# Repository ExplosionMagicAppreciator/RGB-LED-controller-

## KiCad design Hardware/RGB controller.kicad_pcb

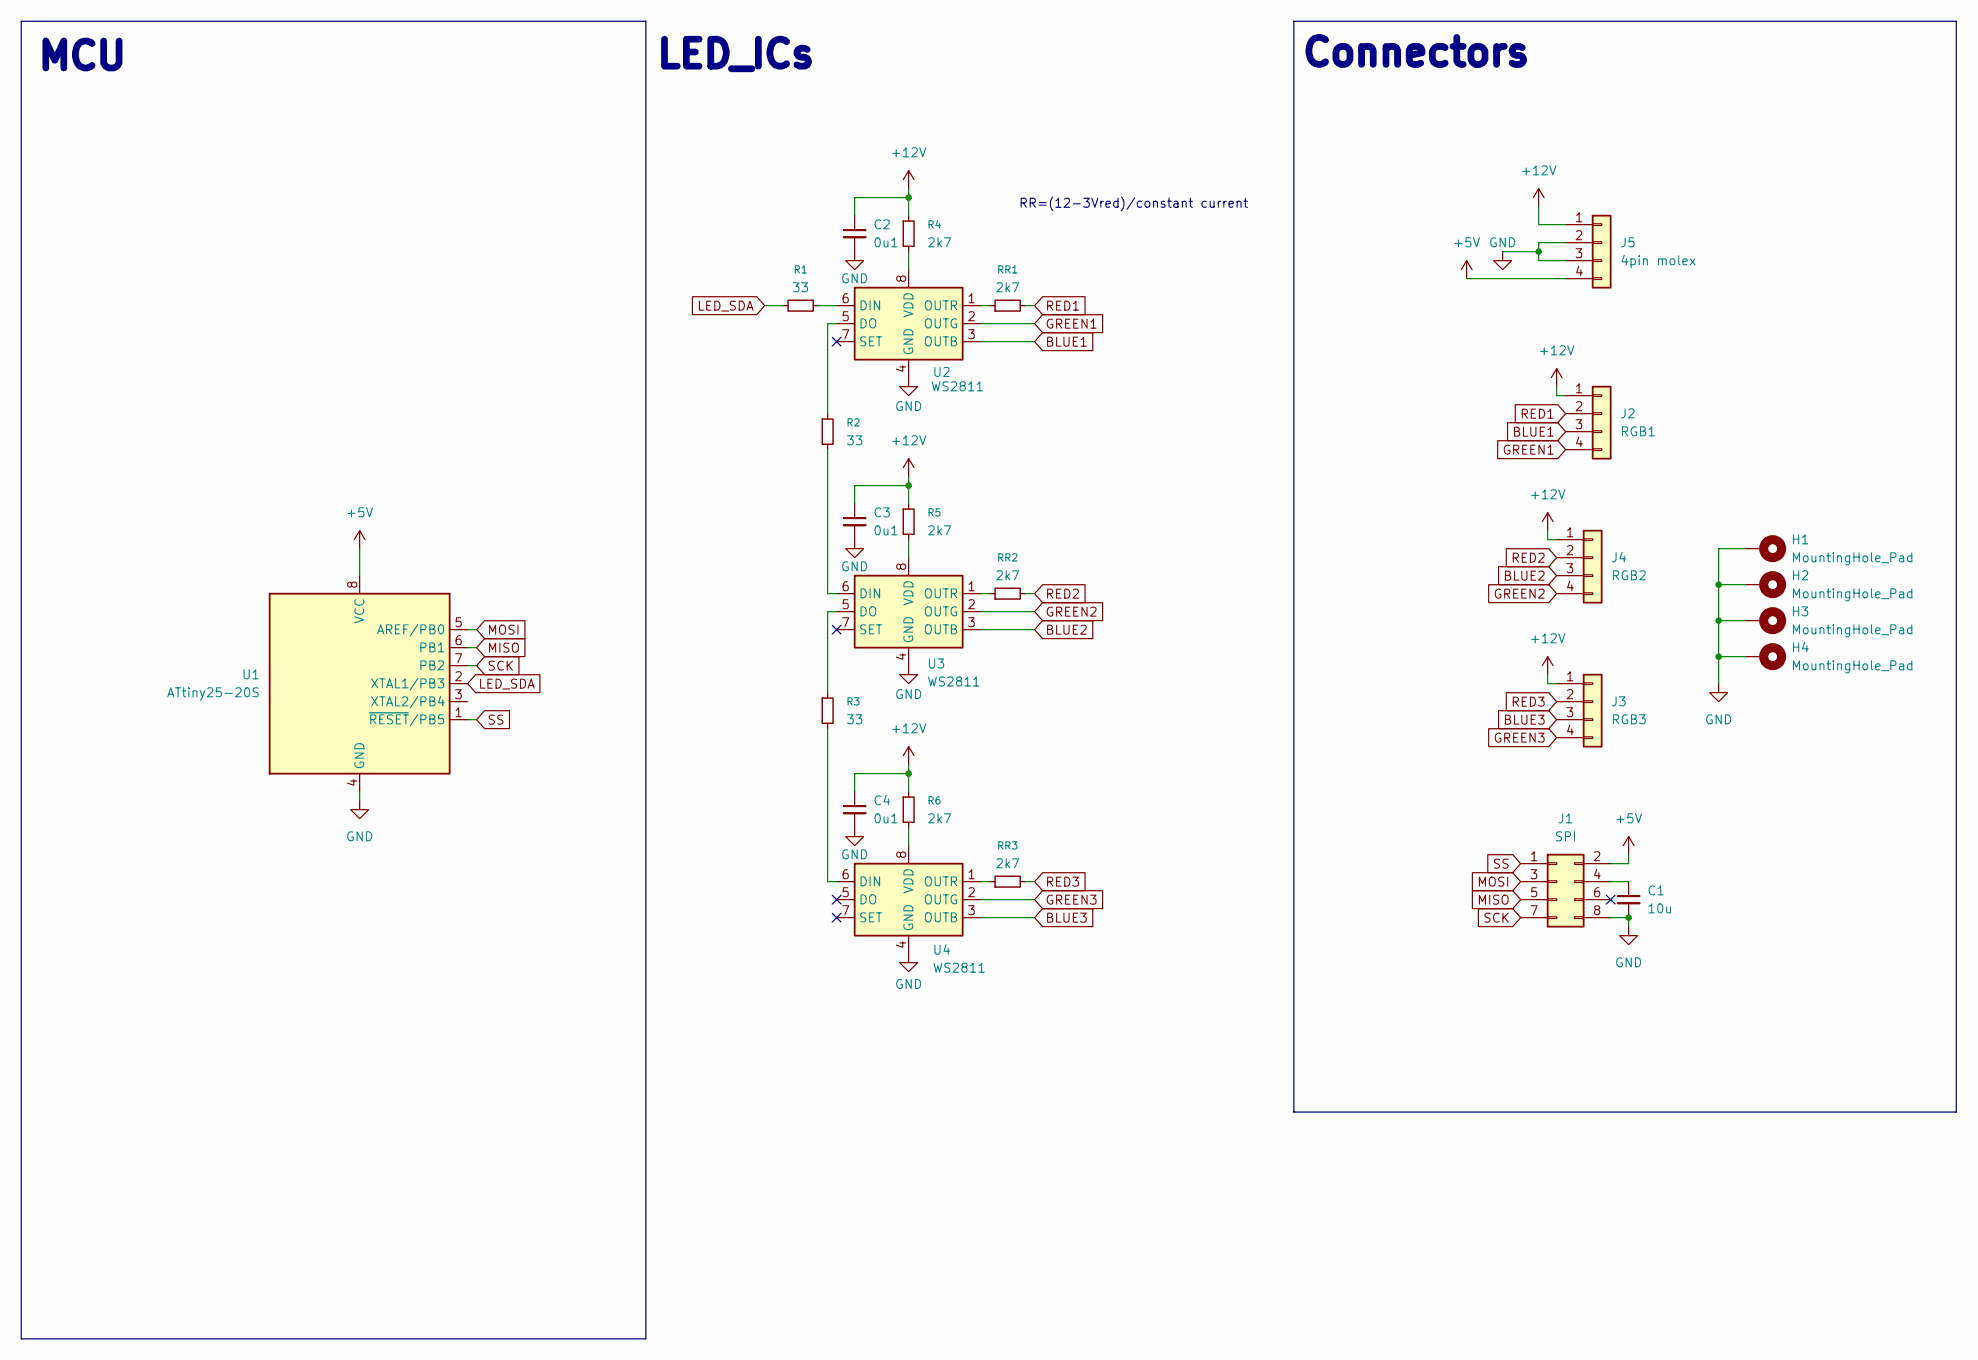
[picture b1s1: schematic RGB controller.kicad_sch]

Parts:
C1: 10u
C2, C3, C4: 0u1
H1, H2, H3, H4: MountingHole_Pad; MountingHole_2.2mm_M2_DIN965_Pad
J1: SPI
J2: RGB1
J3: RGB3
J4: RGB2
J5: 4pin molex
R1, R2, R3: 33
R4, R5, R6: 2k7
RR1, RR2, RR3: 2k7
U1: ATtiny25-20S; SOIC-8_5.3x5.3mm_P1.27mm
U2, U3, U4: WS2811

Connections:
+5V: J1.2, J5.4, U1.8 (VCC)
+12V: C2.1, C3.1, C4.1, J2.1, J3.1, J4.1, J5.1, R4.1, R5.1, R6.1
BLUE1: J2.3, U2.3 (OUTB)
BLUE2: J4.3, U3.3 (OUTB)
BLUE3: J3.3, U4.3 (OUTB)
GND: C1.2, C2.2, C3.2, C4.2, H1.1, H2.1, H3.1, H4.1, J1.8, J5.2, J5.3, U1.4 (GND), U2.4 (GND), U3.4 (GND), U4.4 (GND); also elsewhere on the board
GREEN1: J2.4, U2.2 (OUTG)
GREEN2: J4.4, U3.2 (OUTG)
GREEN3: J3.4, U4.2 (OUTG)
LED_SDA: R1.2, U1.2 (XTAL1/PB3)
MISO: J1.5, U1.6 (PB1); also elsewhere on the board
MOSI: J1.3, U1.5 (AREF/PB0)
unnamed: C1.1, J1.4
unnamed: R1.1, U2.6 (DIN)
unnamed: R2.1, U2.5 (DO)
unnamed: RR1.1, U2.1 (OUTR)
unnamed: R4.2, U2.8 (VDD)
unnamed: R2.2, U3.6 (DIN)
unnamed: R3.1, U3.5 (DO)
unnamed: RR2.1, U3.1 (OUTR)
unnamed: R5.2, U3.8 (VDD)
unnamed: R3.2, U4.6 (DIN)
unnamed: RR3.1, U4.1 (OUTR)
unnamed: R6.2, U4.8 (VDD)
RED1: J2.2, RR1.2
RED2: J4.2, RR2.2
RED3: J3.2, RR3.2
SCK: J1.7, U1.7 (PB2); also elsewhere on the board
SS: J1.1, U1.1 (~RESET/PB5)

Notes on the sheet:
RR=(12-3Vred)/constant current
MCU
Connectors
LED_ICs

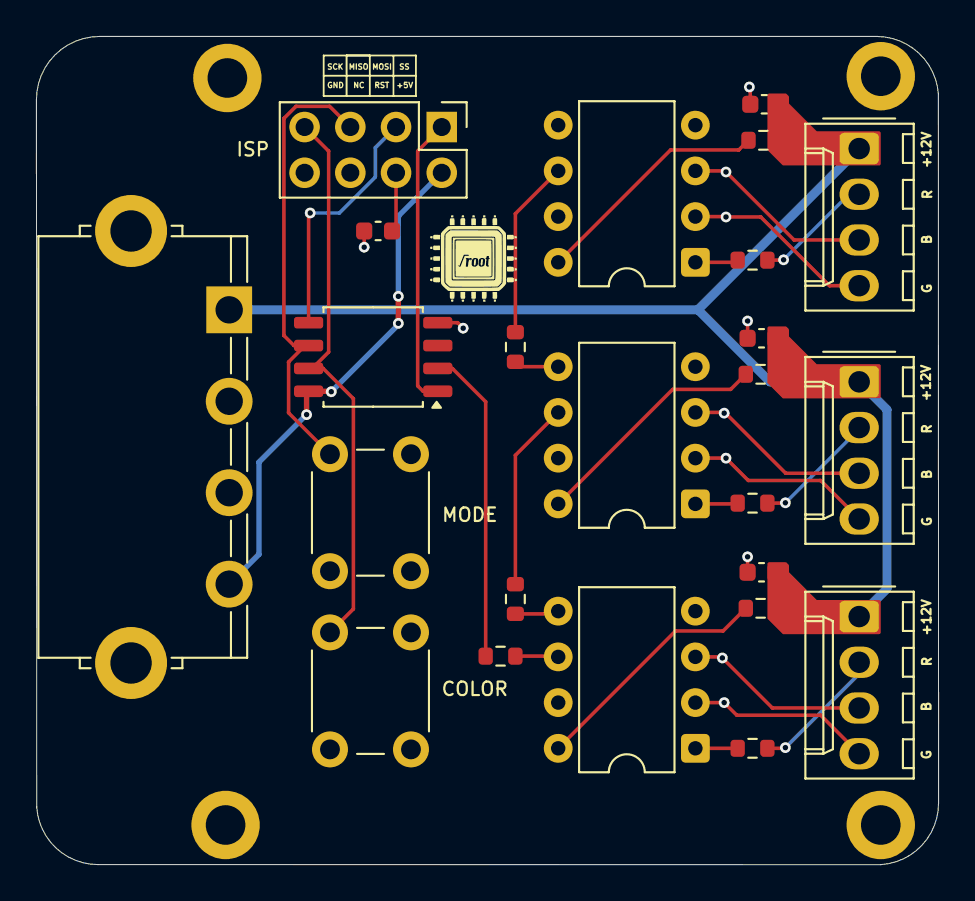
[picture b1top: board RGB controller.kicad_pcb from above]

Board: 2 copper layers, 50.1 x 46.0 mm, 28 parts (0 on the bottom side), 29 nets.

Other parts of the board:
SW1: color; SW_PUSH_6mm_H5mm
SW2: mode; SW_PUSH_6mm_H5mm

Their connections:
GND: SW1.2, SW2.2; also elsewhere on the board
MISO: SW1.1; also elsewhere on the board
SCK: SW2.1; also elsewhere on the board

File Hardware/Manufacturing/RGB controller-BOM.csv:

Reference,Qty,Value,DNP,Exclude from BOM,Exclude from Board,Footprint,Datasheet
C1,1,10u,,,,,~
"C2,C3,C4",3,0u1,,,,,~
J1,1,SPI,,,,,~
J2,1,RGB1,,,,,~
J3,1,RGB3,,,,,~
J4,1,RGB2,,,,,~
J5,1,4pin molex,,,,,~
"R1,R2,R3",3,33,,,,,~
"R4,R5,R6,RR1,RR2,RR3",6,2k7,,,,,~
U1,1,ATtiny25-20S,,,,Package_SO:SOIC-8_5.3x5.3mm_P1.27mm,http://ww1.microchip.com/downloads/en/DeviceDoc/atmel-2586-a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
"U2,U3,U4",3,WS2811,,,,,https://cdn-shop.adafruit.com/datasheets/WS2811.pdf
